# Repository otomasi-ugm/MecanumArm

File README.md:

# Mecanum Robot with Arm 
This repository contain all information to build a Mecanum Robot that have Arm on top of it

## Software
- [Arduino IDE](https://www.arduino.cc/) v1.8.9 <br/>
 ``arduino/mecanum_arm/mecanum_arm.ino``
- [Eagle](https://www.autodesk.com/education/free-software/eagle)

## Hardware
- Teensy 3.5
- H-Bridge motor driver
- Dynamixel Servo AX-18A
- RadioLink GPS
- Telemetri 915Mhz
- Radiolink Remote AT9
- Logitech Cammera C525

## CAD 3D File
- [Here](https://grabcad.com/library/mecanum-arm-manipulator-4-dof-1).

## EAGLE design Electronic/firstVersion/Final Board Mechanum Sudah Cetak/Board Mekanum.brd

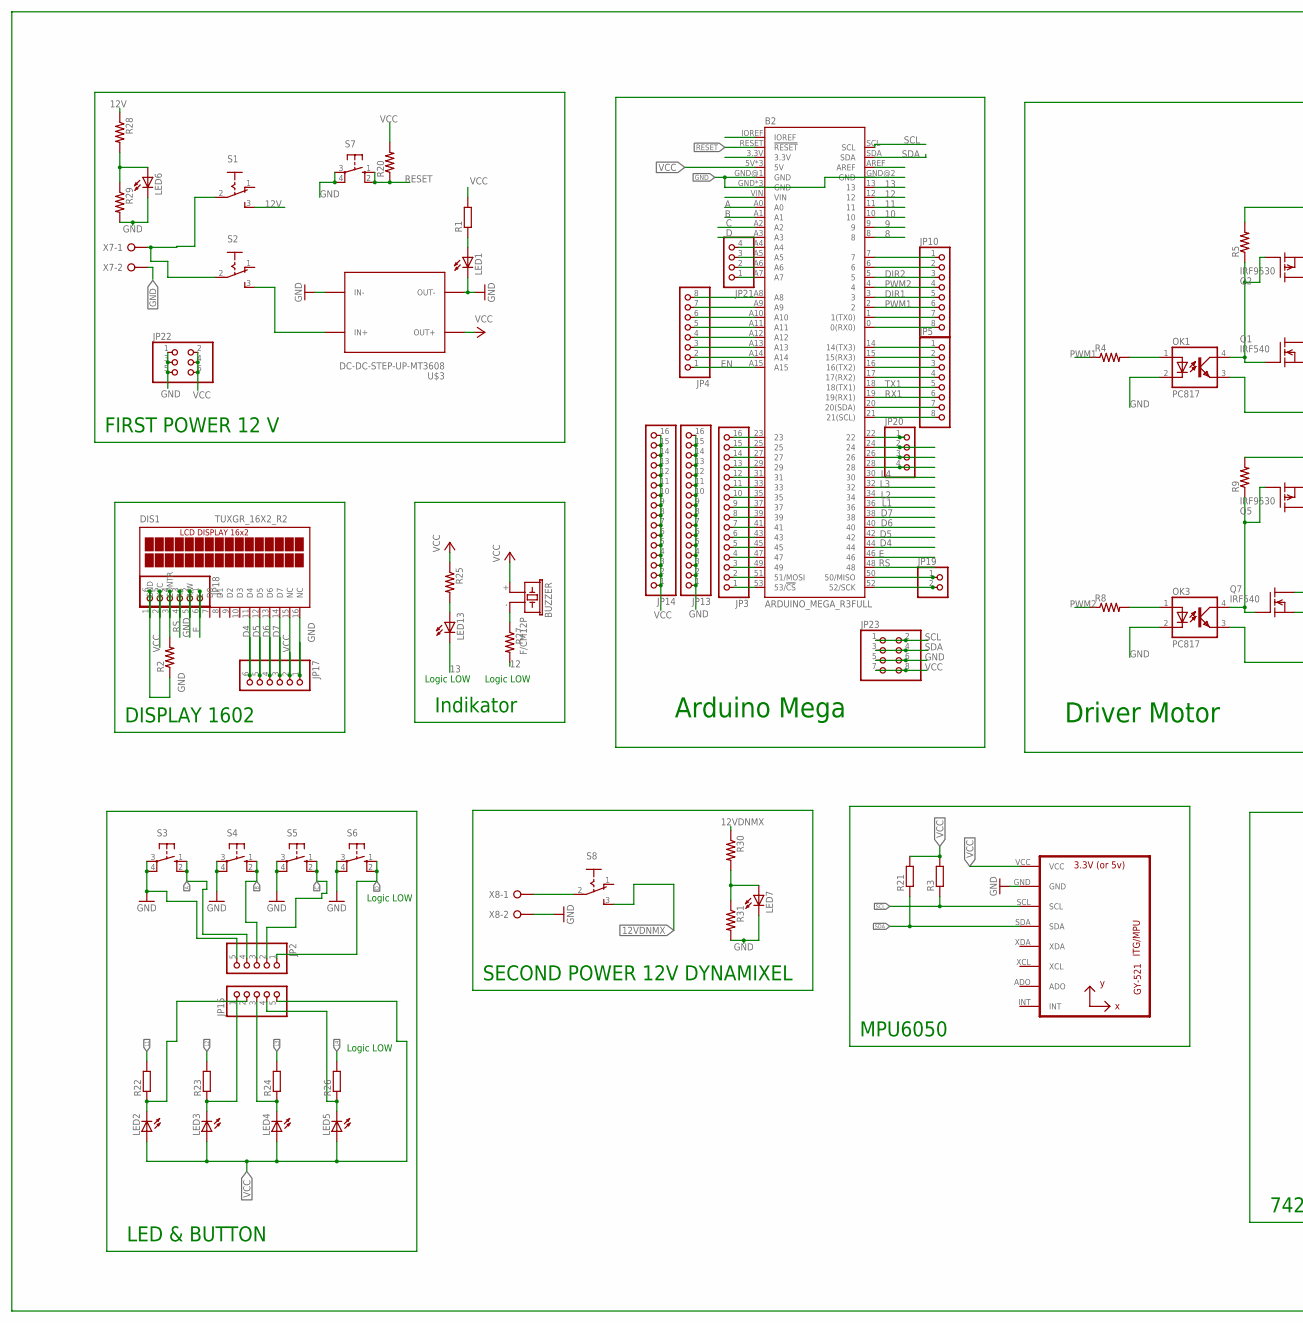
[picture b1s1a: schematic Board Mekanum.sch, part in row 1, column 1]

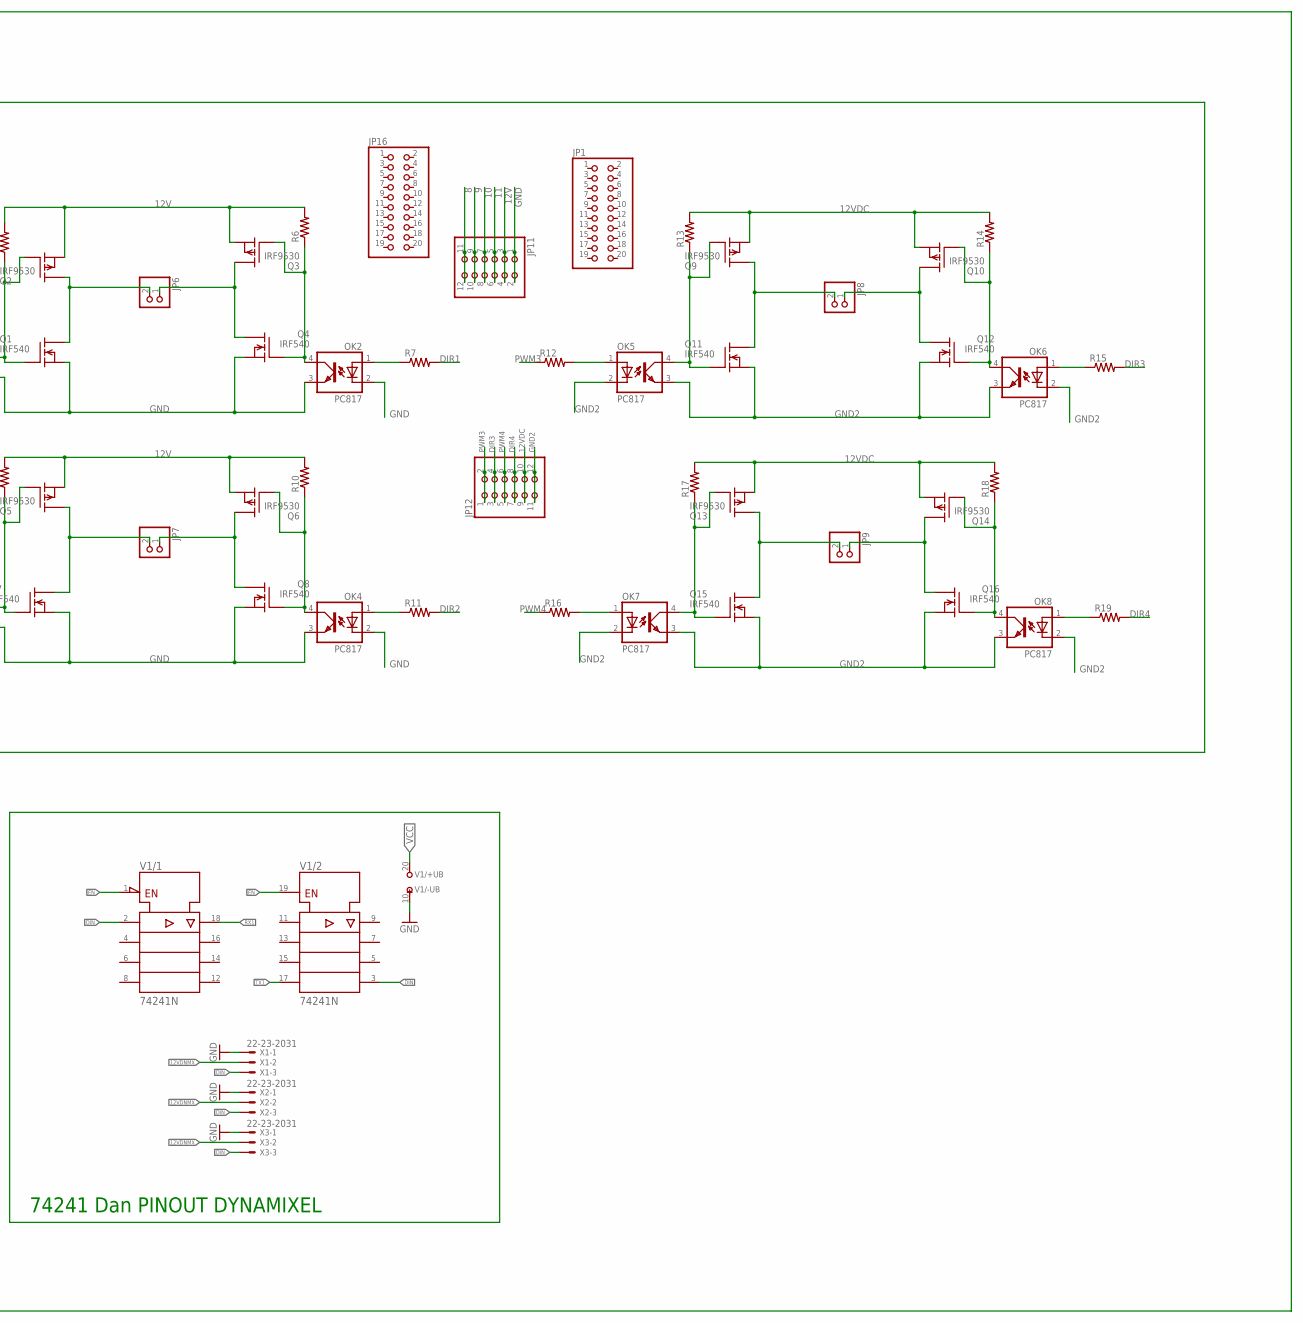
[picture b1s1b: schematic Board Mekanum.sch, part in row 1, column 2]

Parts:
B2: ARDUINO_MEGA_R3FULL; ARDUINO_MEGA_NO_SILK
BUZZER: F/CM12P
DIS1: TUXGR_16X2_R2
JP1, JP16: PINHD-2X10; 2X10
JP2, JP15: PINHD-1X5; 1X05
JP3, JP13, JP14: PINHD-1X16; 1X16
JP4, JP5, JP10: PINHD-1X8; 1X08
JP6, JP7, JP8, JP9, JP19: PINHD-1X2; 1X02
JP11, JP12: PINHD-2X6; 2X06
JP17, JP18: PINHD-1X6; 1X06
JP20, JP21: PINHD-1X4; 1X04
JP22: PINHD-2X3; 2X03
JP23: PINHD-2X4; 2X04
LED1, LED2, LED3, LED4, LED5, LED6, LED7, LED13: LED3MM
OK1, OK3, OK5, OK7: PC817; DIL04
OK2, OK4, OK6, OK8: PC817; DIL04; MPN PC817X4J000F
Q1, Q4, Q7, Q8, Q11, Q12, Q15, Q16: IRF540; TO220
Q2, Q3, Q5, Q6, Q9, Q10, Q13, Q14: IRF9530; TO220
R1: R-EU_0204/7; 0204/7@1
R2, R4, R5, R6, R7, R8, R9, R10, R11, R12, R13, R14, R15, R16, R17, R18, R19, R20, R25, R27: R-US_0207/7; 0207/7
R3, R21, R22, R23, R24, R26: R-EU_0207/7; 0207/7@1
R28, R29, R30, R31: R-US_0207/12; 0207/12
S1, S2, S8: 255SB
S3, S4, S5, S6: 10-XX; B3F-10XX
S7: 10-XX; B3F-10XX; MPN B3F-1000
U1: GY-521MPU6050; GY-521
U$3: DC-DC-STEP-UP-MT3608
V1: 74241N; DIL20
X1, X2, X3: 22-23-2031
X7, X8: W237-02P; W237-132

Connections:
8: B2.8, JP11.11, JP11.12
9: B2.9, JP11.9, JP11.10
10: B2.10, JP11.7, JP11.8
11: B2.11, JP11.5, JP11.6
12: B2.12, R27.2
12V: JP11.3, JP11.4, Q2.3 (S), Q3.3 (S), Q5.3 (S), Q6.3 (S), R5.2, R6.2, R9.2, R10.2, R28.1, S1.3 (S)
12VDC: JP12.9, JP12.10, Q9.3 (S), Q10.3 (S), Q13.3 (S), Q14.3 (S), R13.2, R14.2, R17.2, R18.2
12VDNMX: R30.1, S8.3 (S), X1.2, X2.2, X3.2
13: B2.13, LED13.K (C)
A: B2.A0, JP2.4, S3.1 (S), S3.2 (S1)
B: B2.A1, JP2.3, S4.1 (S), S4.2 (S1)
C: B2.A2, JP2.2, S5.1 (S), S5.2 (S1)
D: B2.A3, JP2.1, S6.1 (S), S6.2 (S1)
D4: B2.44, DIS1.11 (D4), JP17.6
D5: B2.42, DIS1.12 (D5), JP17.5
D6: B2.40, DIS1.13 (D6), JP17.4
D7: B2.38, DIS1.14 (D7), JP17.3
DIN: V1.2 (A1), V1.3 (Y4), X1.3, X2.3, X3.3
DIR1: B2.3, JP10.5, R7.2
DIR2: B2.5, JP10.3, R11.2
DIR3: JP12.3, JP12.4, R15.2
DIR4: JP12.7, JP12.8, R19.2
E: B2.46, DIS1.6 (E), JP18.1
EN: B2.A15, JP4.1, V1.1 (!G), V1.19 (G)
GND: B2.GND, B2.GND@1 (GND), B2.GND@2 (GND), B2.GND@3 (GND), B2.GND@4 (GND), DIS1.1 (GND), DIS1.5 (R/W), DIS1.16 (NC), JP2.5, JP11.1, JP11.2, JP13.1, JP13.2, JP13.3, JP13.4, JP13.5, JP13.6, JP13.7, JP13.8, JP13.9, JP13.10, JP13.11, JP13.12, JP13.13, JP13.14, JP13.15, JP13.16, JP17.1, JP18.2, JP18.6, JP22.1, JP22.3, JP22.5, JP23.5, JP23.6, LED1.K (C), LED6.K (C), LED7.K (C), OK1.2 (C), OK1.3 (EMIT), OK2.2 (C), OK2.3 (EMIT), OK3.2 (C), OK3.3 (EMIT), OK4.2 (C), OK4.3 (EMIT), Q1.3 (S), Q4.3 (S), Q7.3 (S), Q8.3 (S), R2.1, R29.2, R31.2, S3.3, S3.4 (P1), S4.3, S4.4 (P1), S5.3, S5.4 (P1), S6.3, S6.4 (P1), S7.3, S7.4 (P1), U1.GND, U$3.IN-, U$3.OUT-, V1.10 (-UB), X1.1, X2.1, X3.1, X7.2, X8.2
GND2: JP12.11, JP12.12, OK5.2 (C), OK5.3 (EMIT), OK6.2 (C), OK6.3 (EMIT), OK7.2 (C), OK7.3 (EMIT), OK8.2 (C), OK8.3 (EMIT), Q11.3 (S), Q12.3 (S), Q15.3 (S), Q16.3 (S)
L1: B2.36, R22.2
L2: B2.34, R23.2
L3: B2.32, R24.2
L4: B2.30, R26.2
unnamed: BUZZER.- (2), R27.1
unnamed: S1.2, S2.2, X7.1
unnamed: OK1.1 (A), R4.2
unnamed: S2.3 (S), U$3.IN+
unnamed: LED1.A, R1.1
unnamed: OK3.1 (A), R8.2
unnamed: OK1.4 (COL), Q1.1 (G), Q2.1 (G), R5.1
unnamed: JP6.2, Q1.2 (D), Q2.2 (D)
unnamed: OK2.4 (COL), Q3.1 (G), Q4.1 (G), R6.1
unnamed: OK2.1 (A), R7.1
unnamed: OK3.4 (COL), Q5.1 (G), Q7.1 (G), R9.1
unnamed: JP6.1, Q3.2 (D), Q4.2 (D)
unnamed: JP7.2, Q5.2 (D), Q7.2 (D)
unnamed: JP7.1, Q6.2 (D), Q8.2 (D)
unnamed: OK4.4 (COL), Q6.1 (G), Q8.1 (G), R10.1
unnamed: OK4.1 (A), R11.1
unnamed: OK5.1 (A), R12.2
unnamed: OK5.4 (COL), Q9.1 (G), Q11.1 (G), R13.1
unnamed: JP8.2, Q9.2 (D), Q11.2 (D)
unnamed: JP8.1, Q10.2 (D), Q12.2 (D)
unnamed: OK6.4 (COL), Q10.1 (G), Q12.1 (G), R14.1
unnamed: OK6.1 (A), R15.1
unnamed: OK7.1 (A), R16.2
unnamed: OK7.4 (COL), Q13.1 (G), Q15.1 (G), R17.1
unnamed: JP9.2, Q13.2 (D), Q15.2 (D)
unnamed: JP9.1, Q14.2 (D), Q16.2 (D)
unnamed: OK8.4 (COL), Q14.1 (G), Q16.1 (G), R18.1
unnamed: OK8.1 (A), R19.1
unnamed: DIS1.3 (CONTR), JP18.4, R2.2
unnamed: JP15.1, LED2.K (C), R22.1
unnamed: B2.24, JP20.2
unnamed: S8.2, X8.1
unnamed: B2.53 (53/!CS), JP3.1
unnamed: B2.51 (51/MOSI), JP3.2
unnamed: JP15.2, LED3.K (C), R23.1
unnamed: B2.A4, JP21.4
unnamed: B2.A5, JP21.3
unnamed: LED7.A, R30.2, R31.1
unnamed: B2.A8, JP4.8
unnamed: B2.A9, JP4.7
unnamed: B2.A10, JP4.6
unnamed: B2.A11, JP4.5
unnamed: B2.A12, JP4.4
unnamed: B2.A13, JP4.3
unnamed: B2.A14, JP4.2
unnamed: B2.26, JP20.3
unnamed: B2.49, JP3.3
unnamed: B2.47, JP3.4
unnamed: B2.45, JP3.5
unnamed: B2.43, JP3.6
unnamed: B2.28, JP20.4
unnamed: B2.41, JP3.7
unnamed: B2.39, JP3.8
unnamed: B2.37, JP3.9
unnamed: B2.35, JP3.10
unnamed: B2.33, JP3.11
unnamed: B2.31, JP3.12
unnamed: B2.29, JP3.13
unnamed: B2.27, JP3.14
unnamed: B2.25, JP3.15
unnamed: B2.23, JP3.16
unnamed: B2.20 (20(SDA)), JP5.7
unnamed: JP15.3, LED4.K (C), R24.1
unnamed: JP15.4, LED5.K (C), R26.1
unnamed: LED6.A, R28.2, R29.1
unnamed: B2.21 (21(SCL)), JP5.8
unnamed: B2.A7, JP21.1
unnamed: B2.7, JP10.1
unnamed: B2.6, JP10.2
unnamed: B2.A6, JP21.2
unnamed: B2.1 (1(TX0)), JP10.7
unnamed: B2.0 (0(RX0)), JP10.8
unnamed: B2.14 (14(TX3)), JP5.1
unnamed: B2.15 (15(RX3)), JP5.2
unnamed: B2.16 (16(TX2)), JP5.3
unnamed: B2.17 (17(RX2)), JP5.4
unnamed: B2.22, JP20.1
unnamed: B2.50 (50/MISO), JP19.1
unnamed: B2.52 (52/SCK), JP19.2
unnamed: LED13.A, R25.2
PWM1: B2.2, JP10.6, R4.1
PWM2: B2.4, JP10.4, R8.1
PWM3: JP12.1, JP12.2, R12.1
PWM4: JP12.5, JP12.6, R16.1
RESET: B2.RESET (!RESET), R20.1, S7.1 (S), S7.2 (S1)
RS: B2.48, DIS1.4 (RS), JP18.3
RX1: B2.19 (19(RX1)), JP5.6, V1.18 (Y1)
SCL: B2.SCL, JP23.1, JP23.2, R3.1, U1.SCL
SDA: B2.SDA, JP23.3, JP23.4, R21.1, U1.SDA
TX1: B2.18 (18(TX1)), JP5.5, V1.17 (A4)
VCC: B2.5V, B2.5V@1 (5V), B2.5V@2 (5V), BUZZER.+ (1), DIS1.2 (VCC), DIS1.15 (NC), JP14.1, JP14.2, JP14.3, JP14.4, JP14.5, JP14.6, JP14.7, JP14.8, JP14.9, JP14.10, JP14.11, JP14.12, JP14.13, JP14.14, JP14.15, JP14.16, JP15.5, JP17.2, JP18.5, JP22.2, JP22.4, JP22.6, JP23.7, JP23.8, LED2.A, LED3.A, LED4.A, LED5.A, R1.2, R3.2, R20.2, R21.2, R25.1, U1.VCC, U$3.OUT+, V1.20 (+UB)

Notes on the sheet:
Driver Motor
Arduino Mega
FIRST POWER 12 V
Indikator
DISPLAY 1602
MPU6050
LED & BUTTON
74241 Dan PINOUT DYNAMIXEL
Logic LOW
SECOND POWER 12V DYNAMIXEL

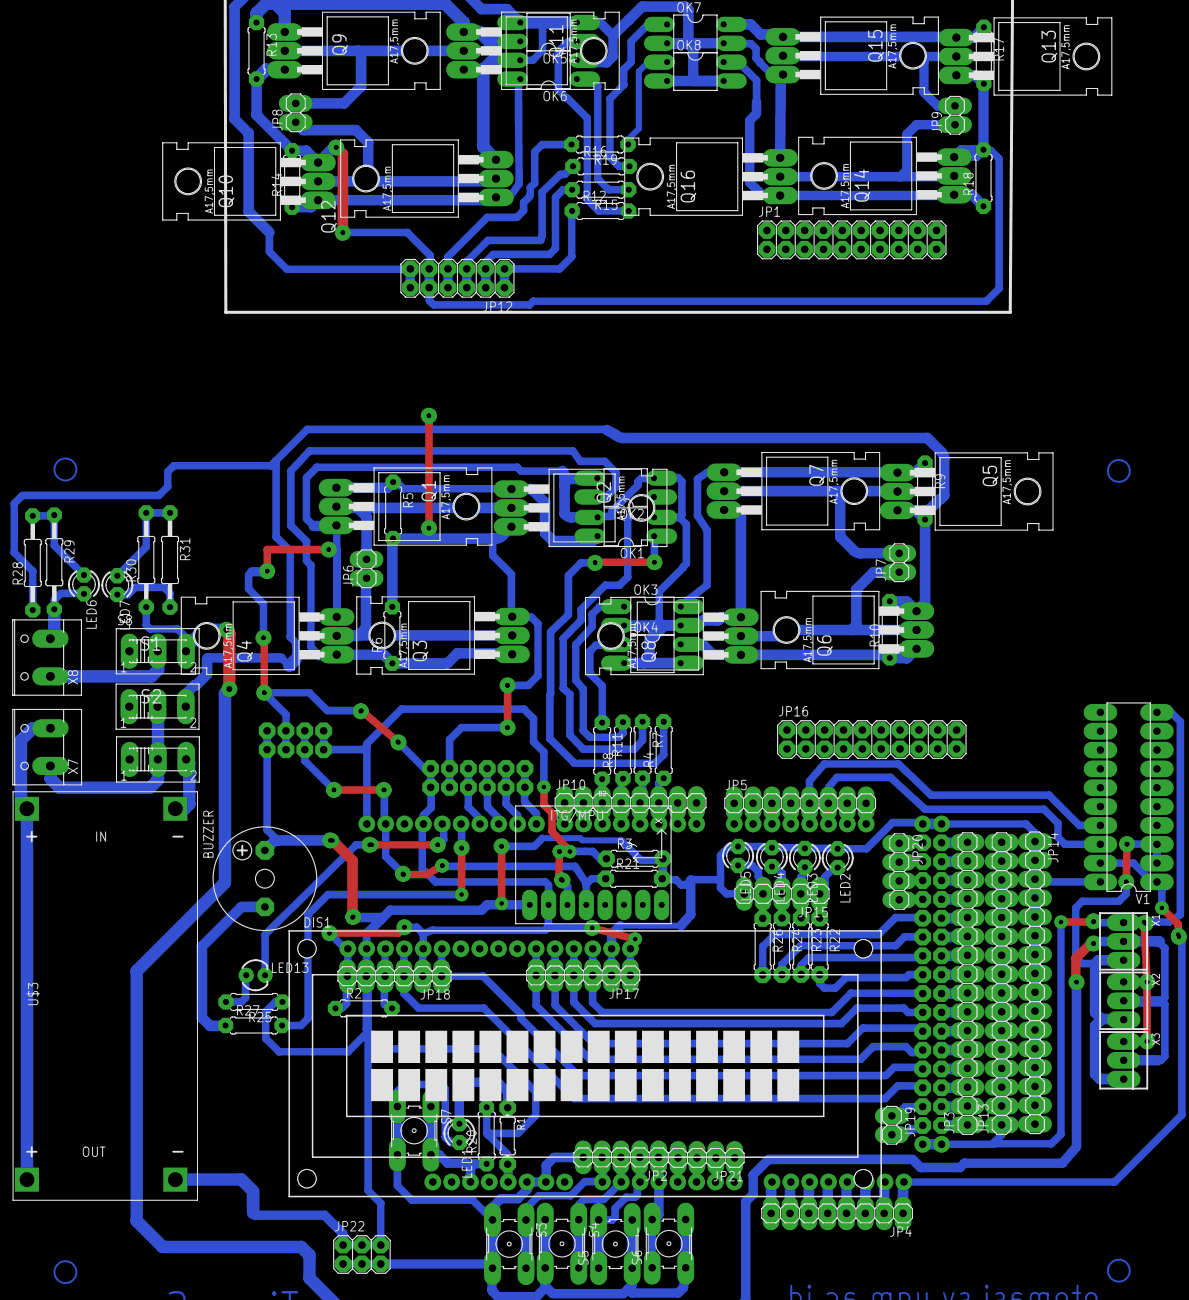
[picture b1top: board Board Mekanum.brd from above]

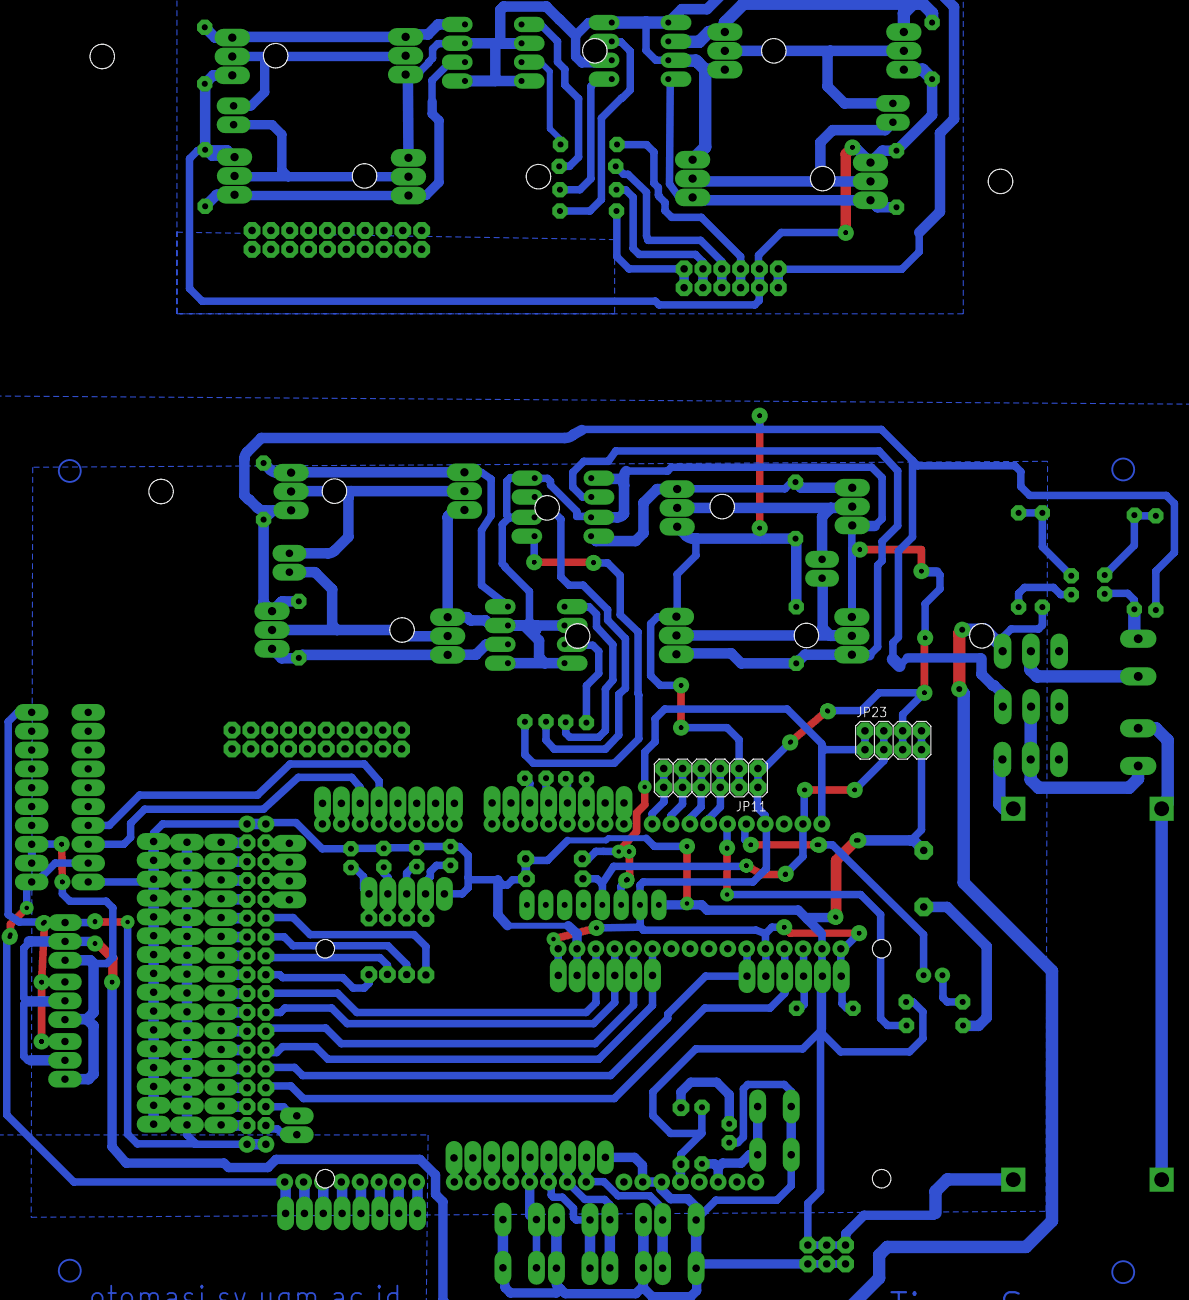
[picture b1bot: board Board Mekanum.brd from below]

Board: 2 copper layers, 105 parts (2 on the bottom side), 121 nets.

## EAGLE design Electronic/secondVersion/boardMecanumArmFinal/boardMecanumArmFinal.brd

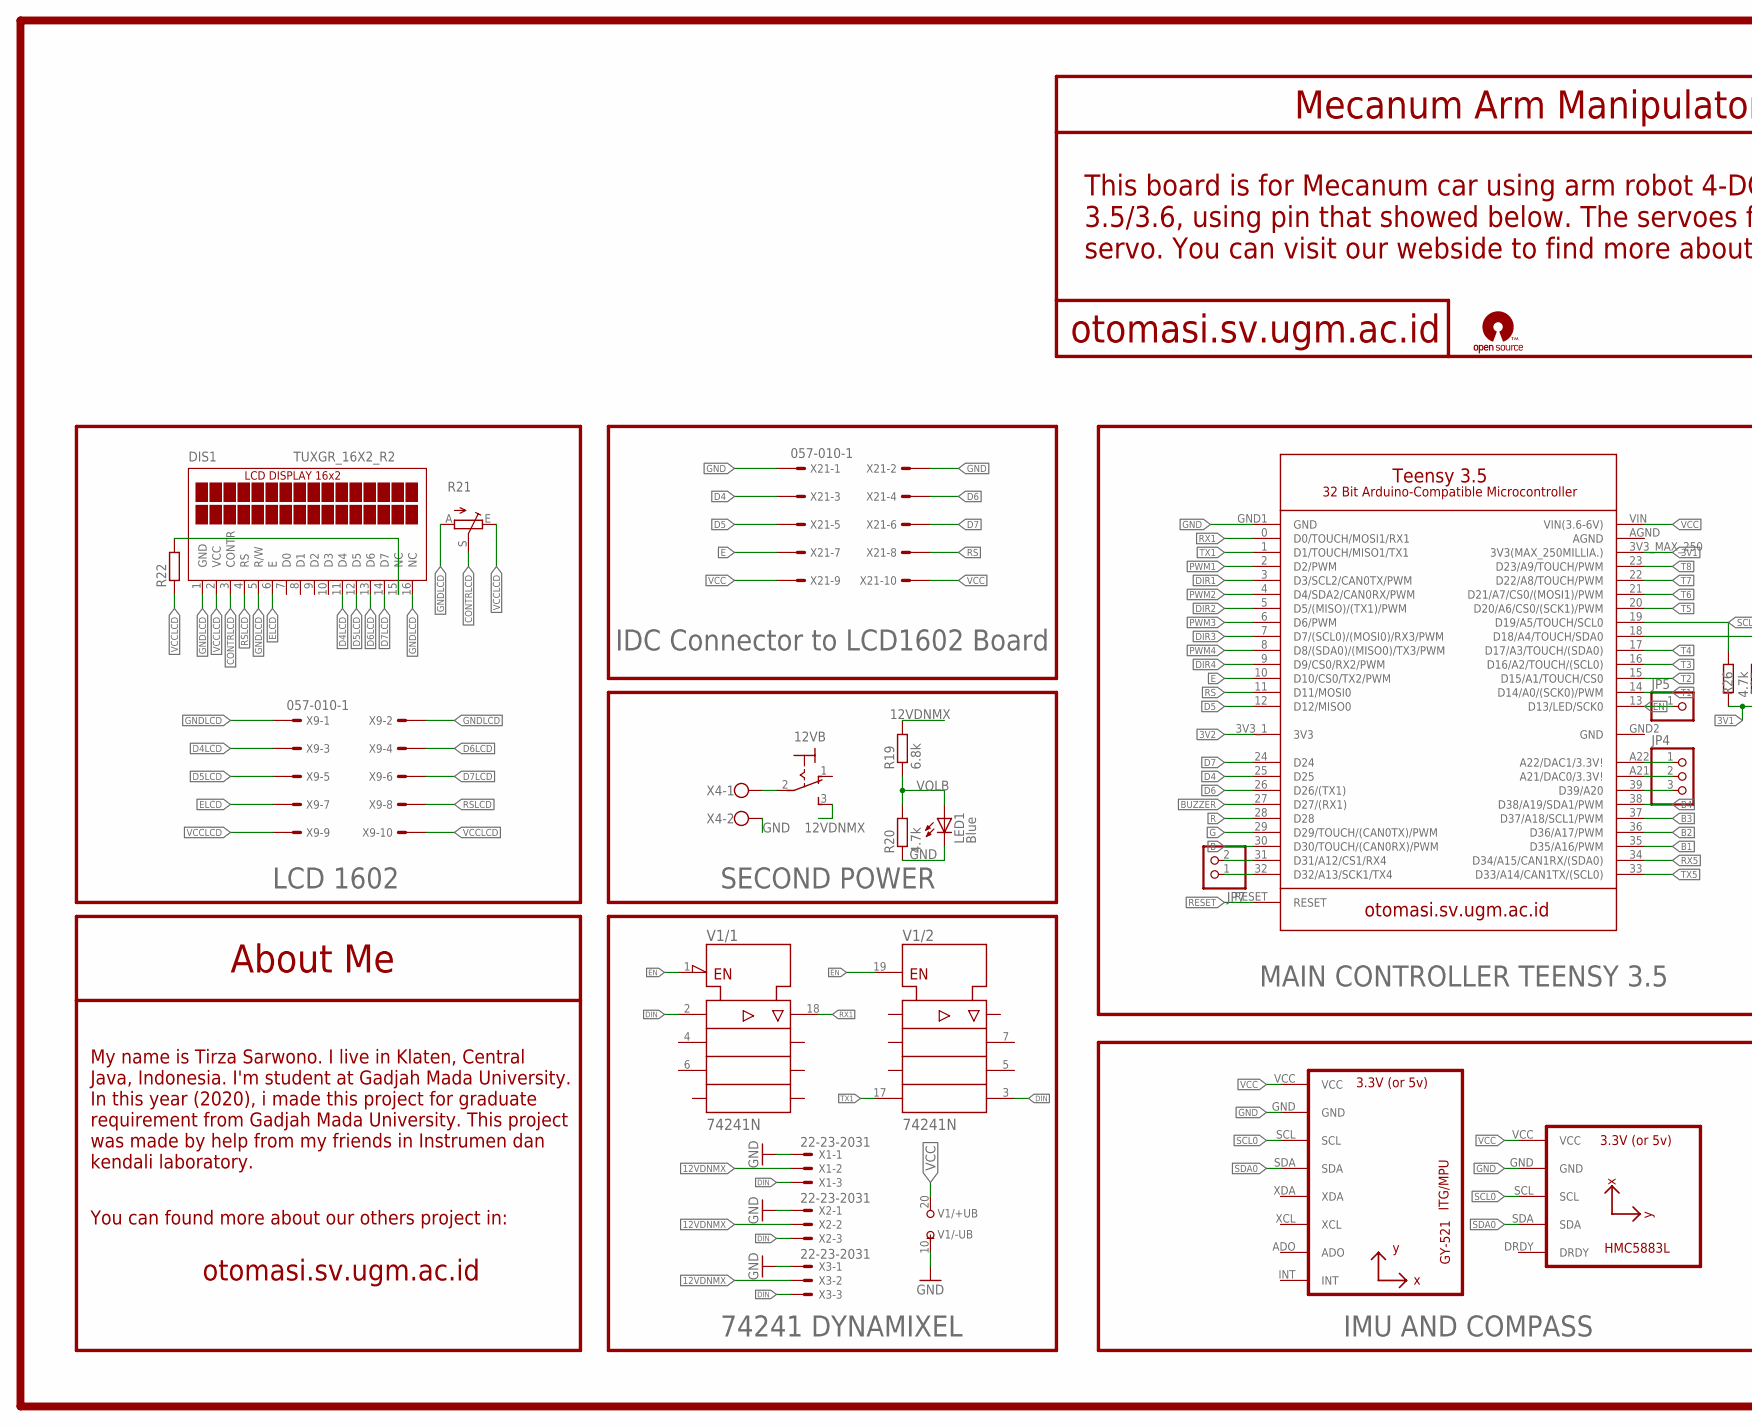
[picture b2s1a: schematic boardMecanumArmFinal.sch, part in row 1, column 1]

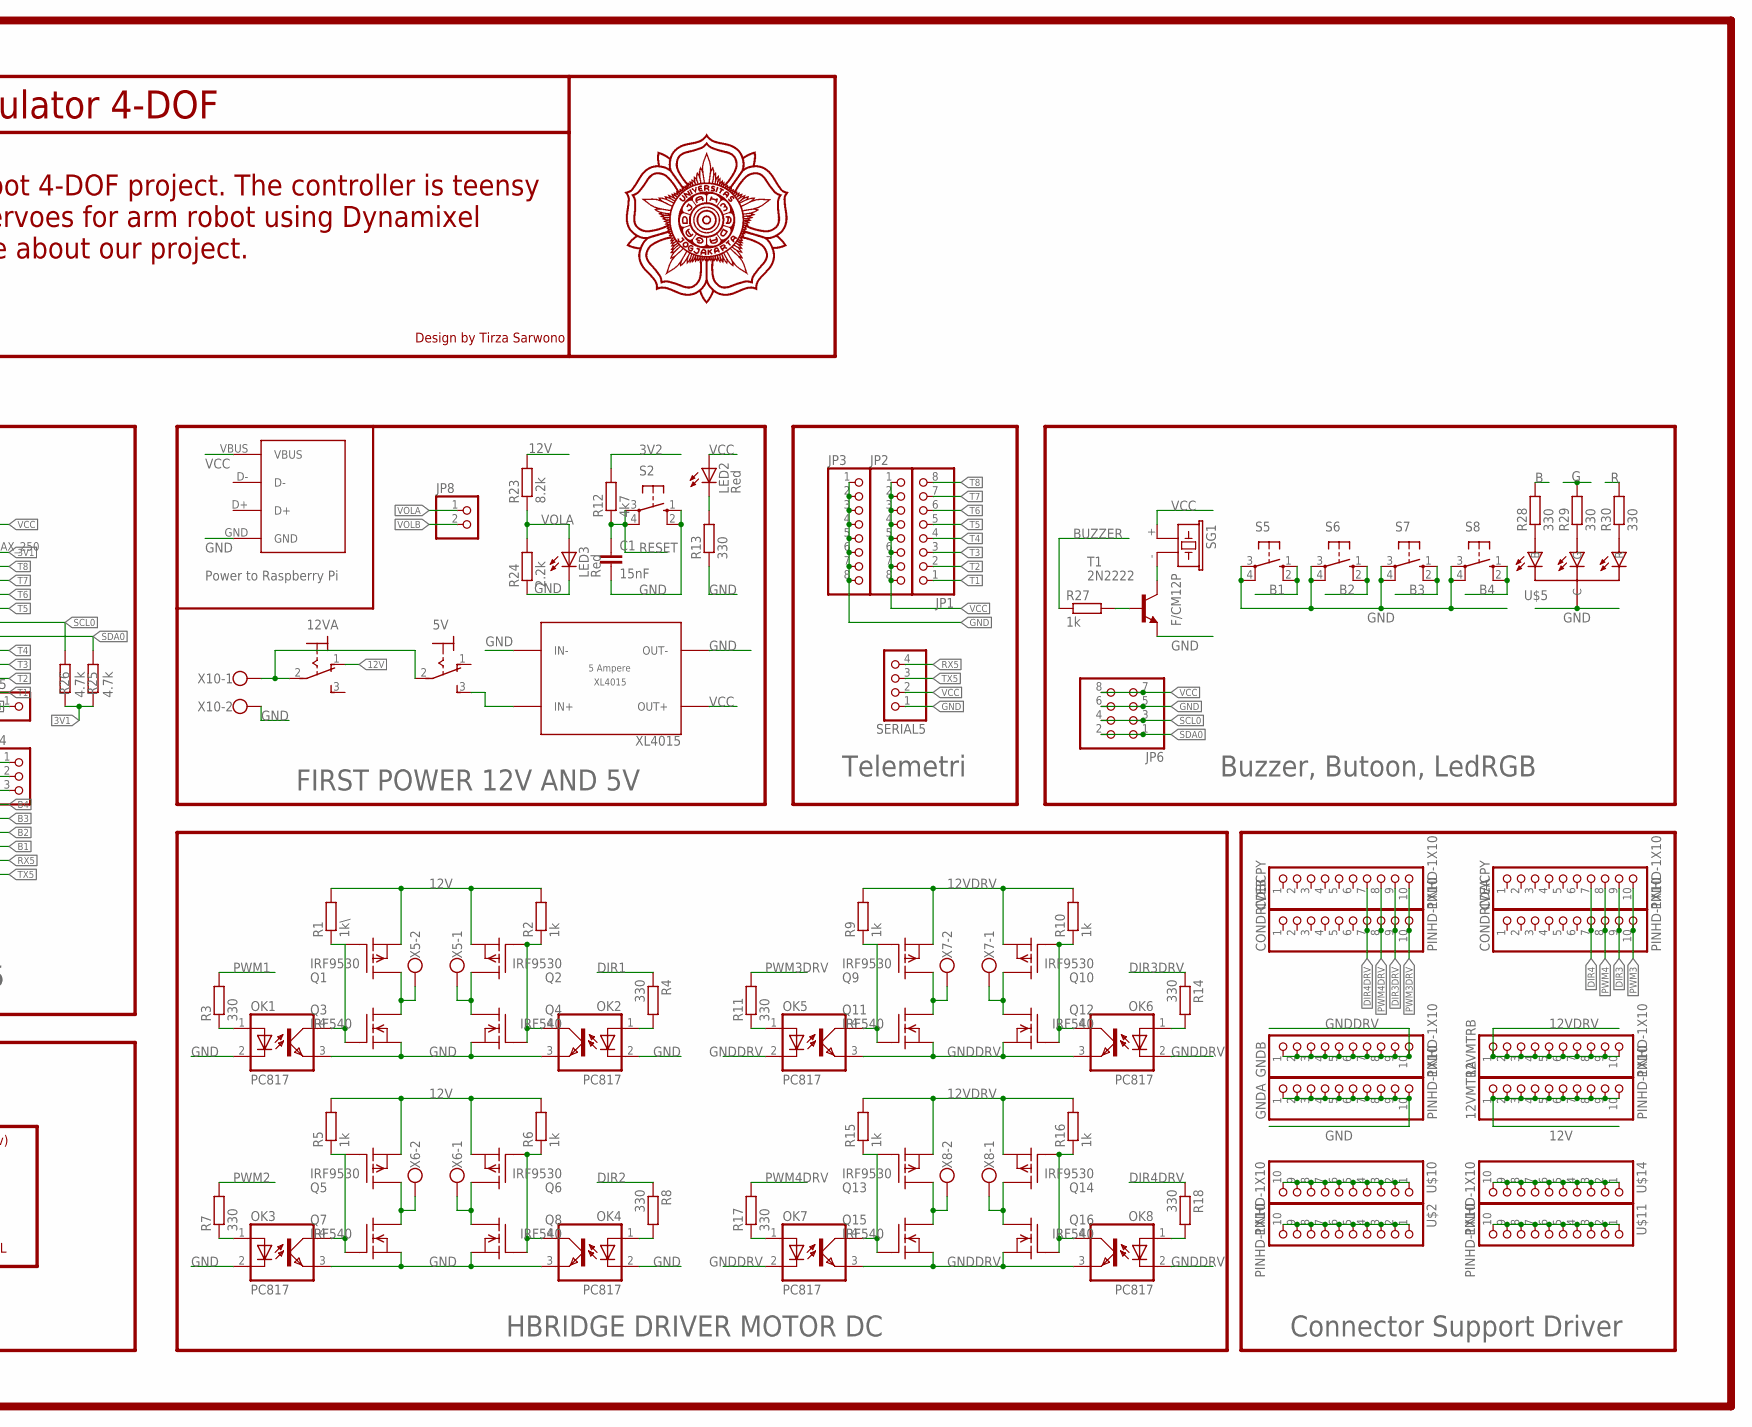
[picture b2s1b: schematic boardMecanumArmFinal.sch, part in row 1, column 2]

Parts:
5V, 12VA, 12VB: M9040P
12VMTRA, 12VMTRB: PINHD-1X10; 1X10-BIG
C1: 15nF; C0805
CDACPY: PINHD-1X10; 1X10-BIG
CDBCPY: PINHD-1X10; 1X10-BIG
CONDRIVEA: PINHD-1X10; 1X10-BIG
CONDRIVEB: PINHD-1X10; 1X10-BIG
DIS1: TUXGR_16X2_R2
GNDA: PINHD-1X10; 1X10-BIG
GNDB: PINHD-1X10; 1X10-BIG
JP1, JP2, JP3: PINHD-1X8BIG; 1X08-BIG
JP4: PINHD-1X3; 1X03
JP5: PINHD-1X1; 1X01
JP6: PINHD-2X4; 2X04
JP7, JP8: PINHD-1X2; 1X02
LED1: Blue; LED3MM
LED2, LED3: Red; LED3MM
OK1, OK2, OK3, OK4, OK5, OK6, OK7, OK8: PC817; DIL04
Q1, Q2, Q5, Q6, Q9, Q10, Q13, Q14: IRF9530; TO220
Q3, Q4, Q7, Q8, Q11, Q12, Q15, Q16: IRF540; TO220
R1: 1k\; 0207/7
R2, R5, R6, R9, R10, R15, R16: 1k; 0207/7
R3, R4, R7, R8, R11, R13, R14, R17, R18: 330; 0207/7
R12: 4k7; R1206
R19: 6.8k; 0207/10
R20: 4.7k; 0207/10
R21: TRIM_EU-B25P; B25P
R22: R-EU_0207/7; 0207/7
R23: 8.2k; 0207/10
R24: 2.2k; 0207/10
R25, R26: 4.7k; R1206
R27: 1k; R1206
R28, R29, R30: 330; R1206
S2, S5, S6, S7, S8: 10-XX; B3F-10XX
SERIAL5: PINHD-1X4; 1X04
SG1: F/CM12P
T1: 2N2222; TO92-EBC-OVAL
U1: HMC5883LMPU6050; HMC5883L
U$1: GY-521MPU6050; GY-521
U$2, U$10, U$11, U$14: PINHD-1X10; 1X10-BIG
U$3: TEENSY_35TEENSY_3.5; TEENSY_35
U$4: FEMALEUSBTODIP
U$5: RGB_CC
V1: 74241N; DIL20
X1, X2, X3: 22-23-2031
X4, X5, X6, X7, X8, X10: W237-102
X9, X21: 057-010-1
XL4015: XL4015

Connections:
3V1: R25.2, R26.2, U$3.3V3_MAX_250 (3V3(MAX_250MILLIA.))
3V2: R12.2, U$3.3V3_1 (3V3)
12V: 12VA.1 (O), 12VMTRA.1, 12VMTRA.2, 12VMTRA.3, 12VMTRA.4, 12VMTRA.5, 12VMTRA.6, 12VMTRA.7, 12VMTRA.8, 12VMTRA.9, 12VMTRA.10, Q1.3 (S), Q2.3 (S), Q5.3 (S), Q6.3 (S), R1.2, R2.2, R5.2, R6.2, R23.2
12VDNMX: 12VB.3 (S), R19.2, X1.2, X2.2, X3.2
12VDRV: 12VMTRB.1, 12VMTRB.2, 12VMTRB.3, 12VMTRB.4, 12VMTRB.5, 12VMTRB.6, 12VMTRB.7, 12VMTRB.8, 12VMTRB.9, 12VMTRB.10, Q9.3 (S), Q10.3 (S), Q13.3 (S), Q14.3 (S), R9.2, R10.2, R15.2, R16.2
AGND: U$3.AGND
B: R28.2, U$3.30 (D30/TOUCH/(CAN0RX)/PWM)
B1: S5.1 (S), S5.2 (S1), U$3.35 (D35/A16/PWM)
B2: S6.1 (S), S6.2 (S1), U$3.36 (D36/A17/PWM)
B3: S7.1 (S), S7.2 (S1), U$3.37 (D37/A18/SCL1/PWM)
B4: S8.1 (S), S8.2 (S1), U$3.38 (D38/A19/SDA1/PWM)
BUZZER: R27.1, U$3.27 (D27/(RX1))
CONTRLCD: DIS1.3 (CONTR), R21.S
D4: U$3.25 (D25), X21.3
D4LCD: DIS1.11 (D4), X9.3
D5: U$3.12 (D12/MISO0), X21.5
D5LCD: DIS1.12 (D5), X9.5
D6: U$3.26 (D26/(TX1)), X21.4
D6LCD: DIS1.13 (D6), X9.4
D7: U$3.24 (D24), X21.6
D7LCD: DIS1.14 (D7), X9.6
DIN: V1.2 (A1), V1.3 (Y4), X1.3, X2.3, X3.3
DIR1: R4.1, U$3.3 (D3/SCL2/CAN0TX/PWM)
DIR2: R8.1, U$3.5 (D5/(MISO)/(TX1)/PWM)
DIR3: CDACPY.9, CONDRIVEA.9, U$3.7 (D7/(SCL0)/(MOSI0)/RX3/PWM)
DIR3DRV: CDBCPY.9, CONDRIVEB.9, R14.1
DIR4: CDACPY.7, CONDRIVEA.7, U$3.9 (D9/CS0/RX2/PWM)
DIR4DRV: CDBCPY.7, CONDRIVEB.7, R18.1
E: U$3.10 (D10/CS0/TX2/PWM), X21.7
ELCD: DIS1.6 (E), X9.7
EN: JP5.1, U$3.13 (D13/LED/SCK0), V1.1 (!G), V1.19 (G)
G: R29.2, U$3.29 (D29/TOUCH/(CAN0TX)/PWM)
GND: C1.2, GNDA.1, GNDA.2, GNDA.3, GNDA.4, GNDA.5, GNDA.6, GNDA.7, GNDA.8, GNDA.9, GNDA.10, JP3.1, JP3.2, JP3.3, JP3.4, JP3.5, JP3.6, JP3.7, JP3.8, JP6.5, JP6.6, LED1.K (C), LED3.K (C), OK1.2 (C), OK1.3 (EMIT), OK2.2 (C), OK2.3 (EMIT), OK3.2 (C), OK3.3 (EMIT), OK4.2 (C), OK4.3 (EMIT), Q3.3 (S), Q4.3 (S), Q7.3 (S), Q8.3 (S), R13.1, R20.1, R24.1, S2.1 (S), S2.2 (S1), S5.3, S5.4 (P1), S6.3, S6.4 (P1), S7.3, S7.4 (P1), S8.3, S8.4 (P1), SERIAL5.1, T1.E, U1.GND, U$1.GND, U$3.GND1 (GND), U$3.GND2 (GND), U$4.GND, U$5.C, V1.10 (-UB), X1.1, X2.1, X3.1, X4.2, X10.2, X21.1, X21.2, XL4015.IN-, XL4015.OUT-
GNDDRV: GNDB.1, GNDB.2, GNDB.3, GNDB.4, GNDB.5, GNDB.6, GNDB.7, GNDB.8, GNDB.9, GNDB.10, OK5.2 (C), OK5.3 (EMIT), OK6.2 (C), OK6.3 (EMIT), OK7.2 (C), OK7.3 (EMIT), OK8.2 (C), OK8.3 (EMIT), Q11.3 (S), Q12.3 (S), Q15.3 (S), Q16.3 (S)
GNDLCD: DIS1.1 (GND), DIS1.5 (R/W), DIS1.16 (NC), R21.A, X9.1, X9.2
unnamed: Q1.2 (D), Q3.2 (D), X5.2
unnamed: Q2.2 (D), Q4.2 (D), X5.1
unnamed: OK1.4 (COL), Q1.1 (G), Q3.1 (G), R1.1
unnamed: Q5.2 (D), Q7.2 (D), X6.2
unnamed: R27.2, T1.B
unnamed: OK2.4 (COL), Q2.1 (G), Q4.1 (G), R2.1
unnamed: Q6.2 (D), Q8.2 (D), X6.1
unnamed: OK3.4 (COL), Q5.1 (G), Q7.1 (G), R5.1
unnamed: OK4.4 (COL), Q6.1 (G), Q8.1 (G), R6.1
unnamed: OK1.1 (A), R3.1
unnamed: OK3.1 (A), R7.1
unnamed: OK2.1 (A), R4.2
unnamed: OK4.1 (A), R8.2
unnamed: Q9.2 (D), Q11.2 (D), X7.2
unnamed: Q10.2 (D), Q12.2 (D), X7.1
unnamed: OK5.4 (COL), Q9.1 (G), Q11.1 (G), R9.1
unnamed: OK6.4 (COL), Q10.1 (G), Q12.1 (G), R10.1
unnamed: OK5.1 (A), R11.1
unnamed: OK6.1 (A), R14.2
unnamed: Q13.2 (D), Q15.2 (D), X8.2
unnamed: Q14.2 (D), Q16.2 (D), X8.1
unnamed: OK7.4 (COL), Q13.1 (G), Q15.1 (G), R15.1
unnamed: OK8.4 (COL), Q14.1 (G), Q16.1 (G), R16.1
unnamed: OK7.1 (A), R17.1
unnamed: OK8.1 (A), R18.2
unnamed: 12VB.2, X4.1
unnamed: JP4.3, U$3.39 (D39/A20)
unnamed: 5V.2, 12VA.2, X10.1
unnamed: 5V.3 (S), XL4015.IN+
unnamed: LED2.K (C), R13.2
unnamed: U$10.1, U$10.2, U$10.3, U$10.4, U$10.5, U$10.6, U$10.7, U$10.8, U$10.9, U$10.10
unnamed: R28.1, U$5.B
unnamed: SG1.- (2), T1.C
unnamed: R29.1, U$5.G
unnamed: R30.1, U$5.R
unnamed: JP4.2, U$3.A21 (A21/DAC0/3.3V!)
unnamed: DIS1.15 (NC), R22.2
unnamed: JP4.1, U$3.A22 (A22/DAC1/3.3V!)
unnamed: U$2.1, U$2.2, U$2.3, U$2.4, U$2.5, U$2.6, U$2.7, U$2.8, U$2.9, U$2.10
unnamed: U$14.1, U$14.2, U$14.3, U$14.4, U$14.5, U$14.6, U$14.7, U$14.8, U$14.9, U$14.10
unnamed: JP7.1, U$3.32 (D32/A13/SCK1/TX4)
unnamed: JP7.2, U$3.31 (D31/A12/CS1/RX4)
unnamed: U$11.1, U$11.2, U$11.3, U$11.4, U$11.5, U$11.6, U$11.7, U$11.8, U$11.9, U$11.10
PWM1: R3.2, U$3.2 (D2/PWM)
PWM2: R7.2, U$3.4 (D4/SDA2/CAN0RX/PWM)
PWM3: CDACPY.10, CONDRIVEA.10, U$3.6 (D6/PWM)
PWM3DRV: CDBCPY.10, CONDRIVEB.10, R11.2
PWM4: CDACPY.8, CONDRIVEA.8, U$3.8 (D8/(SDA0)/(MISO0)/TX3/PWM)
PWM4DRV: CDBCPY.8, CONDRIVEB.8, R17.2
R: R30.2, U$3.28 (D28)
RESET: C1.1, R12.1, S2.3, S2.4 (P1), U$3.RESET
RS: U$3.11 (D11/MOSI0), X21.8
RSLCD: DIS1.4 (RS), X9.8
RX1: U$3.0 (D0/TOUCH/MOSI1/RX1), V1.18 (Y1)
RX5: SERIAL5.4, U$3.34 (D34/A15/CAN1RX/(SDA0))
SCL0: JP6.3, JP6.4, R26.1, U1.SCL, U$1.SCL, U$3.19 (D19/A5/TOUCH/SCL0)
SDA0: JP6.1, JP6.2, R25.1, U1.SDA, U$1.SDA, U$3.18 (D18/A4/TOUCH/SDA0)
T1: JP1.1, U$3.14 (D14/A0/(SCK0)/PWM)
T2: JP1.2, U$3.15 (D15/A1/TOUCH/CS0)
T3: JP1.3, U$3.16 (D16/A2/TOUCH/(SCL0))
T4: JP1.4, U$3.17 (D17/A3/TOUCH/(SDA0))
T5: JP1.5, U$3.20 (D20/A6/CS0/(SCK1)/PWM)
T6: JP1.6, U$3.21 (D21/A7/CS0/(MOSI1)/PWM)
T7: JP1.7, U$3.22 (D22/A8/TOUCH/PWM)
T8: JP1.8, U$3.23 (D23/A9/TOUCH/PWM)
TX1: U$3.1 (D1/TOUCH/MISO1/TX1), V1.17 (A4)
TX5: SERIAL5.3, U$3.33 (D33/A14/CAN1TX/(SCL0))
VCC: JP2.1, JP2.2, JP2.3, JP2.4, JP2.5, JP2.6, JP2.7, JP2.8, JP6.7, JP6.8, LED2.A, SERIAL5.2, SG1.+ (1), U1.VCC, U$1.VCC, U$3.VIN (VIN(3.6-6V)), U$4.VBUS, V1.20 (+UB), X21.9, X21.10, XL4015.OUT+
VCCLCD: DIS1.2 (VCC), R21.E, R22.1, X9.9, X9.10
VOLA: JP8.1, LED3.A, R23.1, R24.2
VOLB: JP8.2, LED1.A, R19.1, R20.2

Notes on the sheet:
74241 DYNAMIXEL
MAIN CONTROLLER TEENSY 3.5
HBRIDGE DRIVER MOTOR DC
SECOND POWER
LCD 1602
IDC Connector to LCD1602 Board
FIRST POWER 12V AND 5V
IMU AND COMPASS
Power to Raspberry Pi
Buzzer, Butoon, LedRGB
Connector Support Driver
Telemetri
Mecanum Arm Manipulator 4-DOF
otomasi.sv.ugm.ac.id
Design by Tirza Sarwono
This board is for Mecanum car using arm robot 4-DOF project. The controller is teensy 3.5/3.6, using pin that showed below. The servoes for arm robot using Dynamixel servo. You can visit our webside to find more about our project.
About Me
My name is Tirza Sarwono. I live in Klaten, Central Java, Indonesia. I'm student at Gadjah Mada University. In this year (2020), i made this project for graduate requirement from Gadjah Mada University. This project was made by help from my friends in Instrumen dan kendali laboratory.
You can found more about our others project in:

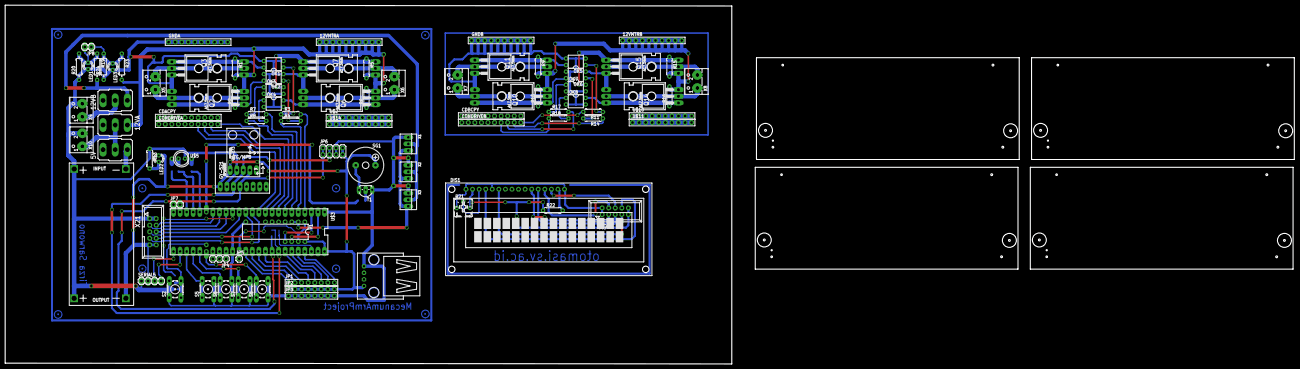
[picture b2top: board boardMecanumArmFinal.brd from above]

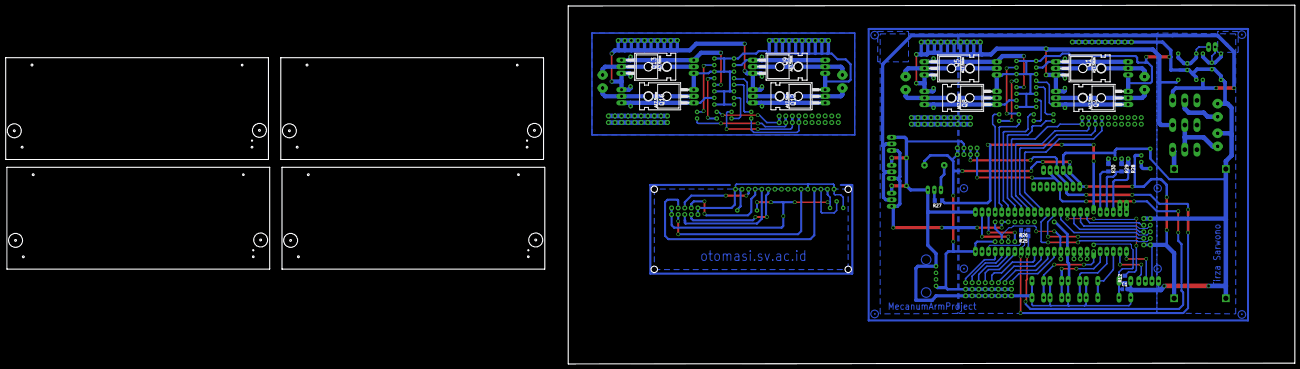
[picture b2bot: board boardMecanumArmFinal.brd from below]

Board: 2 copper layers, 281.0 x 138.7 mm, 108 parts (16 on the bottom side), 105 nets.

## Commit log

2019-09-22 First version
2019-09-22 Change Arduino Mega configuration
2019-09-22 First version (#1)
    * First version
    * Change Arduino Mega configuration
2020-07-29 add second version

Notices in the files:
parts and their libraries:
SparkFun-Boards: Licensing: Creative Commons ShareAlike 4.0 International - https://creativecommons.org/licenses/by-sa/4.0
SparkFun: Licensing: CC v3.0 Share-Alike You are welcome to use this library for commercial purposes.
